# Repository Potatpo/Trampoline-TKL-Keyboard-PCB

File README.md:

# The Trampoline TKL Keyboard PCB
The trampoline tkl pcb features split spacebar, a rotary encoder, and a usb daughterboard.

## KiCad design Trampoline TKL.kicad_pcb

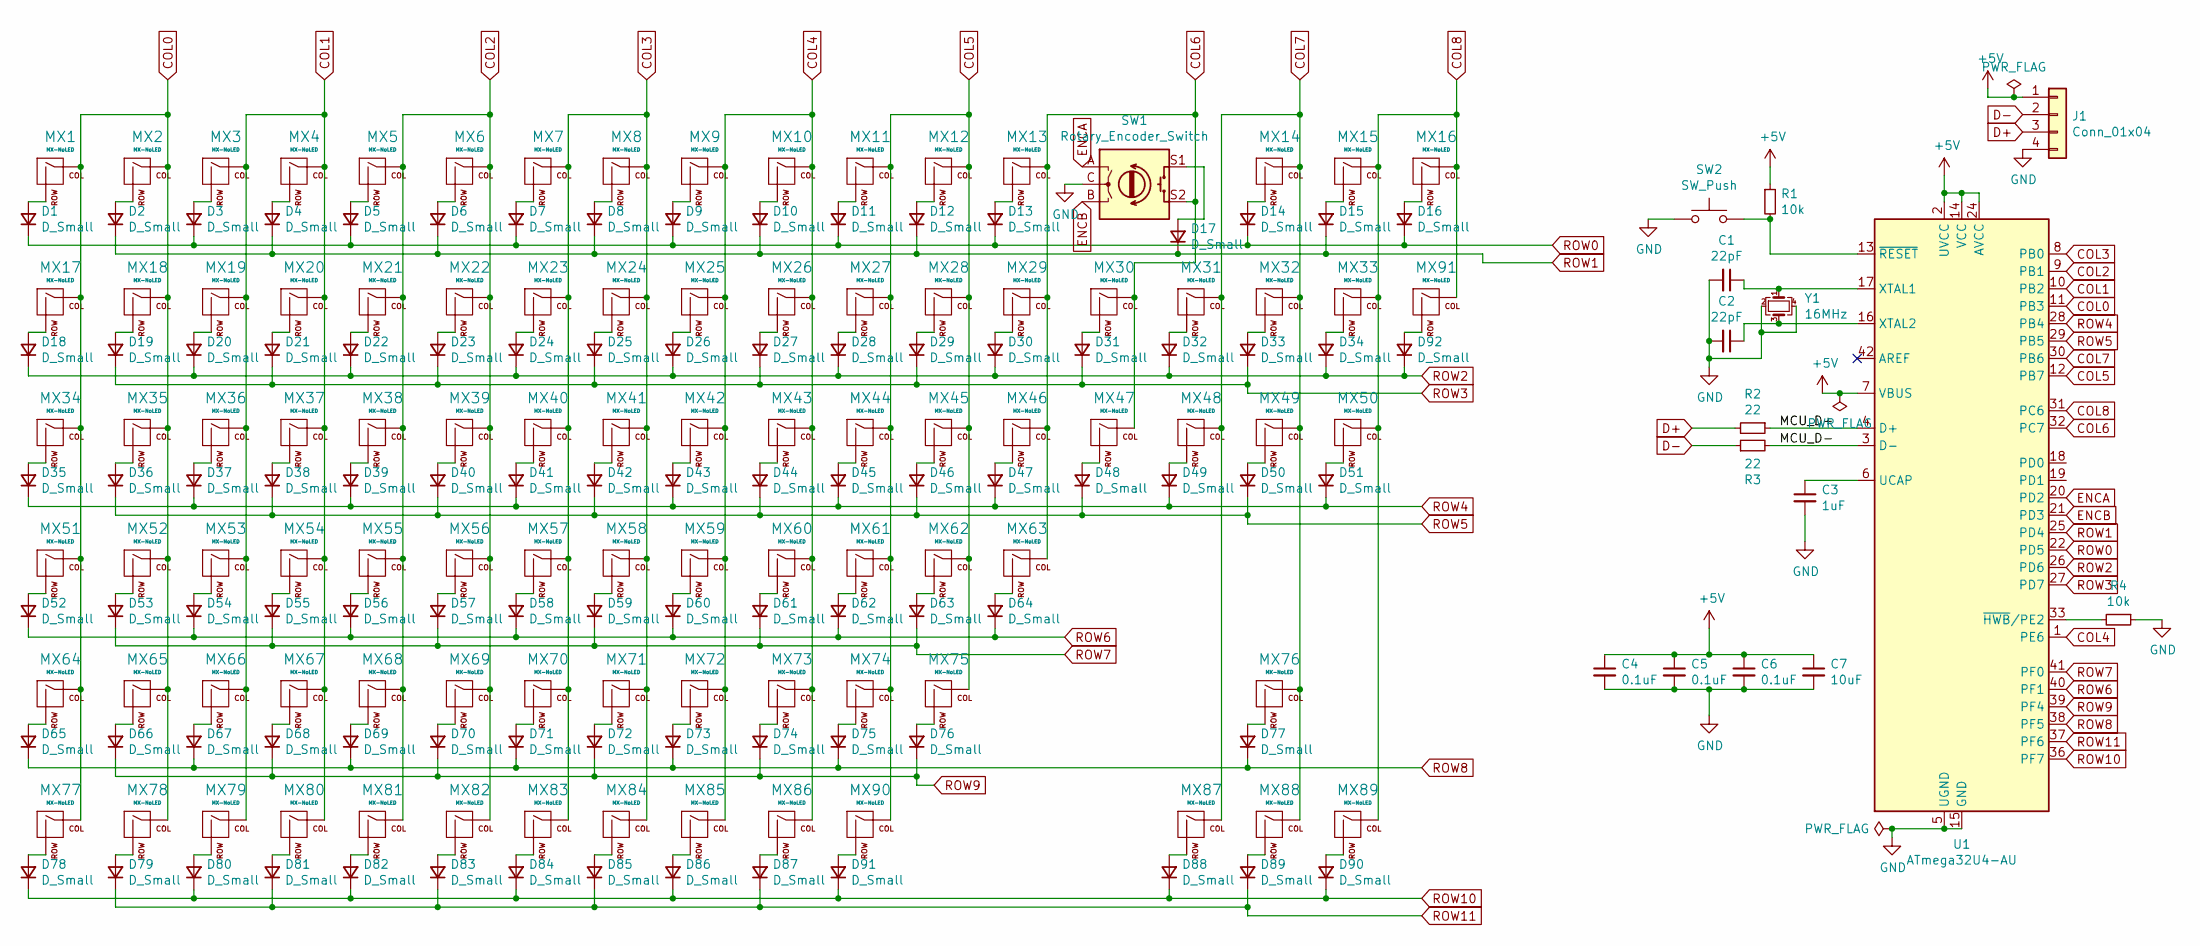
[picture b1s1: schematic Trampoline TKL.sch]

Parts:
C1, C2: 22pF; C_0805_2012Metric
C3: 1uF; C_0805_2012Metric
C4, C5, C6: 0.1uF; C_0805_2012Metric
C7: 10uF; C_0805_2012Metric
D1, D2, D3, D4, D5, D6, D7, D8, D9, D10, D11, D12, D13, D14, D15, D16, D17, D18, D19, D20, D21, D22, D23, D24, D25, D26, D27, D28, D29, D30, D31, D32, D33, D34, D35, D36, D37, D38, D39, D40, D41, D42, D43, D44, D45, D46, D47, D48, D49, D50, D51, D52, D53, D54, D55, D56, D57, D58, D59, D60, D61, D62, D63, D64, D65, D66, D67, D68, D69, D70, D71, D72, D73, D74, D75, D76, D77, D78, D79, D80, D81, D82, D83, D84, D85, D86, D87, D88, D89, D90, D91, D92: D_Small; D_SOD-123
J1: Conn_01x04; JST_SH_SM04B-SRSS-TB_1x04-1MP_P1.00mm_Horizontal
MX1, MX2, MX3, MX4, MX5, MX6, MX7, MX8, MX9, MX10, MX11, MX12, MX13, MX14, MX15, MX16, MX17, MX18, MX19, MX20, MX21, MX22, MX23, MX24, MX25, MX26, MX27, MX28, MX29, MX31, MX32, MX33, MX35, MX36, MX37, MX38, MX39, MX40, MX41, MX42, MX43, MX44, MX45, MX46, MX48, MX49, MX50, MX52, MX53, MX54, MX55, MX56, MX57, MX58, MX59, MX60, MX61, MX62, MX65, MX66, MX67, MX68, MX69, MX70, MX71, MX72, MX73, MX74, MX76, MX87, MX88, MX89, MX91: MX-NoLED; MXOnly-1U-NoLED
MX30: MX-NoLED; MXOnly-2U-NoLED
MX34, MX47: MX-NoLED; MXOnly-1.5U-NoLED
MX51: MX-NoLED; MXOnly-1.75U-NoLED
MX63, MX64, MX80: MX-NoLED; MXOnly-2.25U-NoLED
MX75, MX83: MX-NoLED; MXOnly-2.75U-NoLED
MX77, MX78, MX79, MX81, MX84, MX85, MX86, MX90: MX-NoLED; MXOnly-1.25U-NoLED
MX82: MX-NoLED; MXOnly-6.25U-NoLED
R1, R4: 10k; R_0805_2012Metric
R2, R3: 22; R_0805_2012Metric
SW1: Rotary_Encoder_Switch; RotaryEncoder_Alps_EC11E-Switch_Vertical_H20mm
SW2: SW_Push; SW_SPST_TL3342
U1: ATmega32U4-AU; TQFP-44_10x10mm_P0.8mm
Y1: 16MHz; Crystal_SMD_3225-4Pin_3.2x2.5mm

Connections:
+5V: C4.1, C5.1, C6.1, C7.1, J1.1, R1.1, U1.2 (UVCC), U1.7 (VBUS), U1.14 (VCC), U1.24 (AVCC), U1.34 (VCC), U1.44 (AVCC)
/MCU_D+: R2.1, U1.4 (D+)
/MCU_D-: R3.2, U1.3 (D-)
COL0: MX1.1 (COL), MX2.1 (COL), MX17.1 (COL), MX18.1 (COL), MX34.1 (COL), MX35.1 (COL), MX51.1 (COL), MX52.1 (COL), MX64.1 (COL), MX65.1 (COL), MX77.1 (COL), MX78.1 (COL), U1.11 (PB3)
COL1: MX3.1 (COL), MX4.1 (COL), MX19.1 (COL), MX20.1 (COL), MX36.1 (COL), MX37.1 (COL), MX53.1 (COL), MX54.1 (COL), MX66.1 (COL), MX67.1 (COL), MX79.1 (COL), MX80.1 (COL), U1.10 (PB2)
COL2: MX5.1 (COL), MX6.1 (COL), MX21.1 (COL), MX22.1 (COL), MX38.1 (COL), MX39.1 (COL), MX55.1 (COL), MX56.1 (COL), MX68.1 (COL), MX69.1 (COL), MX81.1 (COL), MX82.1 (COL), U1.9 (PB1)
COL3: MX7.1 (COL), MX8.1 (COL), MX23.1 (COL), MX24.1 (COL), MX40.1 (COL), MX41.1 (COL), MX57.1 (COL), MX58.1 (COL), MX70.1 (COL), MX71.1 (COL), MX83.1 (COL), MX84.1 (COL), U1.8 (PB0)
COL4: MX9.1 (COL), MX10.1 (COL), MX25.1 (COL), MX26.1 (COL), MX42.1 (COL), MX43.1 (COL), MX59.1 (COL), MX60.1 (COL), MX72.1 (COL), MX73.1 (COL), MX85.1 (COL), MX86.1 (COL), U1.1 (PE6)
COL5: MX11.1 (COL), MX12.1 (COL), MX27.1 (COL), MX28.1 (COL), MX44.1 (COL), MX45.1 (COL), MX61.1 (COL), MX62.1 (COL), MX74.1 (COL), MX75.1 (COL), MX90.1 (COL), U1.12 (PB7)
COL6: MX13.1 (COL), MX29.1 (COL), MX30.1 (COL), MX46.1 (COL), MX47.1 (COL), MX63.1 (COL), SW1.S2, U1.32 (PC7)
COL7: MX14.1 (COL), MX31.1 (COL), MX32.1 (COL), MX48.1 (COL), MX49.1 (COL), MX76.1 (COL), MX87.1 (COL), MX88.1 (COL), U1.30 (PB6)
COL8: MX15.1 (COL), MX16.1 (COL), MX33.1 (COL), MX50.1 (COL), MX89.1 (COL), MX91.1 (COL), U1.31 (PC6)
D+: J1.3, R2.2
D-: J1.2, R3.1
ENCA: SW1.A, U1.20 (PD2)
ENCB: SW1.B, U1.21 (PD3)
GND: C1.2, C2.2, C3.2, C4.2, C5.2, C6.2, C7.2, J1.4, R4.1, SW1.C, SW2.1, U1.5 (UGND), U1.15 (GND), U1.23 (GND), U1.35 (GND), U1.43 (GND), Y1.2, Y1.4
unnamed: C1.1, U1.17 (XTAL1), Y1.1
unnamed: C2.1, U1.16 (XTAL2), Y1.3
unnamed: C3.1, U1.6 (UCAP)
unnamed: D1.2 (A), MX1.2 (ROW)
unnamed: D2.2 (A), MX2.2 (ROW)
unnamed: D3.2 (A), MX3.2 (ROW)
unnamed: D4.2 (A), MX4.2 (ROW)
unnamed: D5.2 (A), MX5.2 (ROW)
unnamed: D6.2 (A), MX6.2 (ROW)
unnamed: D7.2 (A), MX7.2 (ROW)
unnamed: D8.2 (A), MX8.2 (ROW)
unnamed: D9.2 (A), MX9.2 (ROW)
unnamed: D10.2 (A), MX10.2 (ROW)
unnamed: D11.2 (A), MX11.2 (ROW)
unnamed: D12.2 (A), MX12.2 (ROW)
unnamed: D13.2 (A), MX13.2 (ROW)
unnamed: D14.2 (A), MX14.2 (ROW)
unnamed: D15.2 (A), MX15.2 (ROW)
unnamed: D16.2 (A), MX16.2 (ROW)
unnamed: D17.2 (A), SW1.S1
unnamed: D18.2 (A), MX17.2 (ROW)
unnamed: D19.2 (A), MX18.2 (ROW)
unnamed: D20.2 (A), MX19.2 (ROW)
unnamed: D21.2 (A), MX20.2 (ROW)
unnamed: D22.2 (A), MX21.2 (ROW)
unnamed: D23.2 (A), MX22.2 (ROW)
unnamed: D24.2 (A), MX23.2 (ROW)
unnamed: D25.2 (A), MX24.2 (ROW)
unnamed: D26.2 (A), MX25.2 (ROW)
unnamed: D27.2 (A), MX26.2 (ROW)
unnamed: D28.2 (A), MX27.2 (ROW)
unnamed: D29.2 (A), MX28.2 (ROW)
unnamed: D30.2 (A), MX29.2 (ROW)
unnamed: D31.2 (A), MX30.2 (ROW)
unnamed: D32.2 (A), MX31.2 (ROW)
unnamed: D33.2 (A), MX32.2 (ROW)
unnamed: D34.2 (A), MX33.2 (ROW)
unnamed: D35.2 (A), MX34.2 (ROW)
unnamed: D36.2 (A), MX35.2 (ROW)
unnamed: D37.2 (A), MX36.2 (ROW)
unnamed: D38.2 (A), MX37.2 (ROW)
unnamed: D39.2 (A), MX38.2 (ROW)
unnamed: D40.2 (A), MX39.2 (ROW)
unnamed: D41.2 (A), MX40.2 (ROW)
unnamed: D42.2 (A), MX41.2 (ROW)
unnamed: D43.2 (A), MX42.2 (ROW)
unnamed: D44.2 (A), MX43.2 (ROW)
unnamed: D45.2 (A), MX44.2 (ROW)
unnamed: D46.2 (A), MX45.2 (ROW)
unnamed: D47.2 (A), MX46.2 (ROW)
unnamed: D48.2 (A), MX47.2 (ROW)
unnamed: D49.2 (A), MX48.2 (ROW)
unnamed: D50.2 (A), MX49.2 (ROW)
unnamed: D51.2 (A), MX50.2 (ROW)
unnamed: D52.2 (A), MX51.2 (ROW)
unnamed: D53.2 (A), MX52.2 (ROW)
unnamed: D54.2 (A), MX53.2 (ROW)
unnamed: D55.2 (A), MX54.2 (ROW)
unnamed: D56.2 (A), MX55.2 (ROW)
unnamed: D57.2 (A), MX56.2 (ROW)
unnamed: D58.2 (A), MX57.2 (ROW)
unnamed: D59.2 (A), MX58.2 (ROW)
unnamed: D60.2 (A), MX59.2 (ROW)
unnamed: D61.2 (A), MX60.2 (ROW)
unnamed: D62.2 (A), MX61.2 (ROW)
unnamed: D63.2 (A), MX62.2 (ROW)
unnamed: D64.2 (A), MX63.2 (ROW)
unnamed: D65.2 (A), MX64.2 (ROW)
unnamed: D66.2 (A), MX65.2 (ROW)
unnamed: D67.2 (A), MX66.2 (ROW)
unnamed: D68.2 (A), MX67.2 (ROW)
unnamed: D69.2 (A), MX68.2 (ROW)
unnamed: D70.2 (A), MX69.2 (ROW)
unnamed: D71.2 (A), MX70.2 (ROW)
unnamed: D72.2 (A), MX71.2 (ROW)
unnamed: D73.2 (A), MX72.2 (ROW)
unnamed: D74.2 (A), MX73.2 (ROW)
unnamed: D75.2 (A), MX74.2 (ROW)
unnamed: D76.2 (A), MX75.2 (ROW)
unnamed: D77.2 (A), MX76.2 (ROW)
unnamed: D78.2 (A), MX77.2 (ROW)
unnamed: D79.2 (A), MX78.2 (ROW)
unnamed: D80.2 (A), MX79.2 (ROW)
unnamed: D81.2 (A), MX80.2 (ROW)
unnamed: D82.2 (A), MX81.2 (ROW)
unnamed: D83.2 (A), MX82.2 (ROW)
unnamed: D84.2 (A), MX83.2 (ROW)
unnamed: D85.2 (A), MX84.2 (ROW)
unnamed: D86.2 (A), MX85.2 (ROW)
unnamed: D87.2 (A), MX86.2 (ROW)
unnamed: D88.2 (A), MX87.2 (ROW)
unnamed: D89.2 (A), MX88.2 (ROW)
unnamed: D90.2 (A), MX89.2 (ROW)
unnamed: D91.2 (A), MX90.2 (ROW)
unnamed 111: D92.2 (A), MX91.2 (ROW); also elsewhere on the board
unnamed: R1.2, SW2.2, U1.13 (~RESET)
unnamed: R4.2, U1.33 (~HWB~/PE2)
ROW0: D1.1 (K), D3.1 (K), D5.1 (K), D7.1 (K), D9.1 (K), D11.1 (K), D13.1 (K), D14.1 (K), D16.1 (K), U1.22 (PD5)
ROW1: D2.1 (K), D4.1 (K), D6.1 (K), D8.1 (K), D10.1 (K), D12.1 (K), D15.1 (K), D17.1 (K), U1.25 (PD4)
ROW2: D18.1 (K), D20.1 (K), D22.1 (K), D24.1 (K), D26.1 (K), D28.1 (K), D30.1 (K), D32.1 (K), D34.1 (K), D92.1 (K), U1.26 (PD6); also elsewhere on the board
ROW3: D19.1 (K), D21.1 (K), D23.1 (K), D25.1 (K), D27.1 (K), D29.1 (K), D31.1 (K), D33.1 (K), U1.27 (PD7)
ROW4: D35.1 (K), D37.1 (K), D39.1 (K), D41.1 (K), D43.1 (K), D45.1 (K), D47.1 (K), D49.1 (K), D51.1 (K), U1.28 (PB4)
ROW5: D36.1 (K), D38.1 (K), D40.1 (K), D42.1 (K), D44.1 (K), D46.1 (K), D48.1 (K), D50.1 (K), U1.29 (PB5)
ROW6: D52.1 (K), D54.1 (K), D56.1 (K), D58.1 (K), D60.1 (K), D62.1 (K), D64.1 (K), U1.40 (PF1)
ROW7: D53.1 (K), D55.1 (K), D57.1 (K), D59.1 (K), D61.1 (K), D63.1 (K), U1.41 (PF0)
ROW8: D65.1 (K), D67.1 (K), D69.1 (K), D71.1 (K), D73.1 (K), D75.1 (K), D77.1 (K), U1.38 (PF5)
ROW9: D66.1 (K), D68.1 (K), D70.1 (K), D72.1 (K), D74.1 (K), D76.1 (K), U1.39 (PF4)
ROW10: D78.1 (K), D80.1 (K), D82.1 (K), D84.1 (K), D86.1 (K), D88.1 (K), D90.1 (K), D91.1 (K), U1.36 (PF7)
ROW11: D79.1 (K), D81.1 (K), D83.1 (K), D85.1 (K), D87.1 (K), D89.1 (K), U1.37 (PF6)

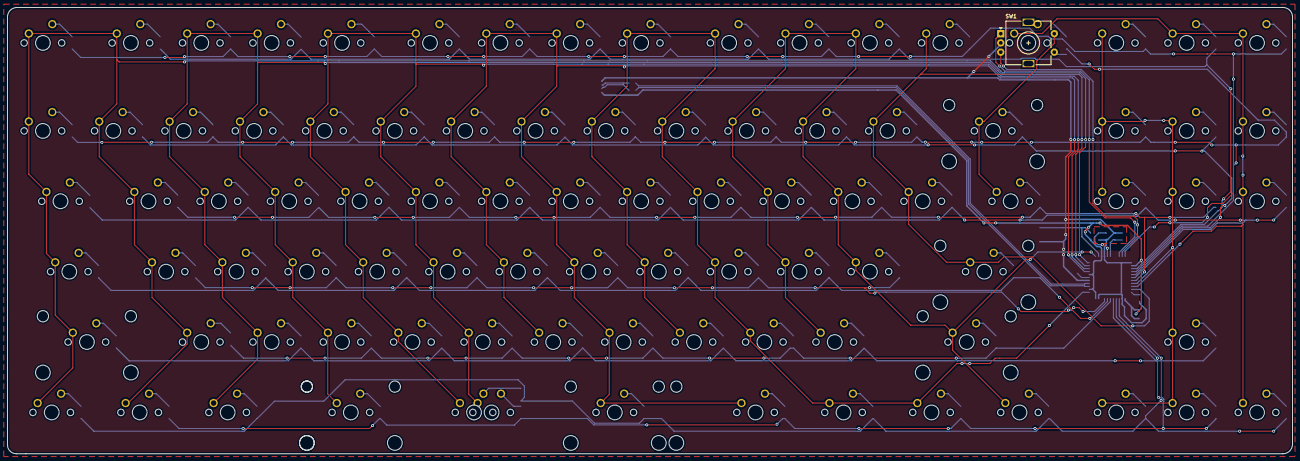
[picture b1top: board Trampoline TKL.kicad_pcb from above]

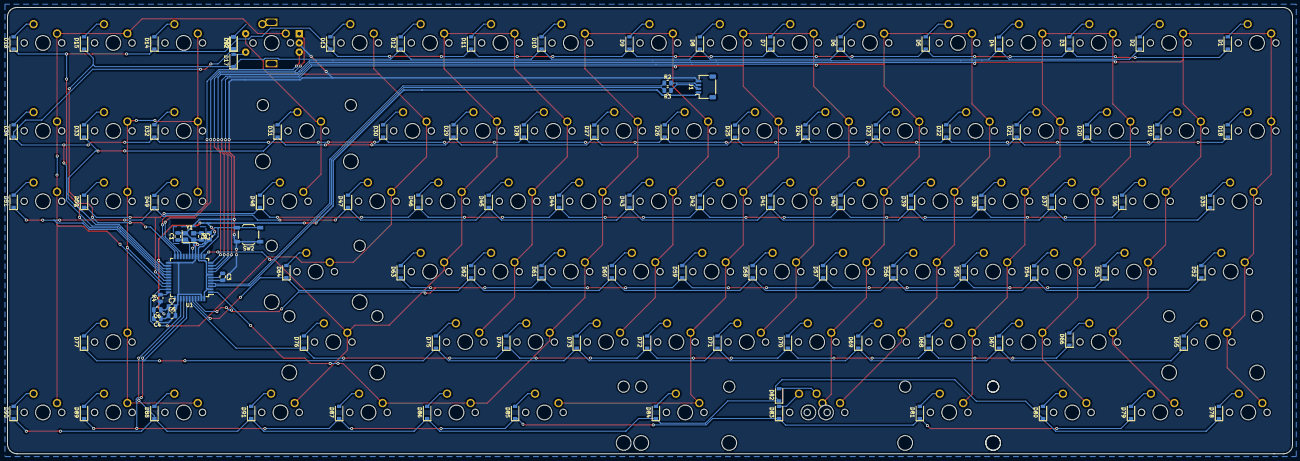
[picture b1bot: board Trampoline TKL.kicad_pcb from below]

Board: 2 copper layers, 347.8 x 120.8 mm, 200 parts (108 on the bottom side), 126 nets.

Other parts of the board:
D92#2: D_Small; D_SOD-123

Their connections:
unnamed 111: D92#2.2; also elsewhere on the board
ROW2: D92#2.1; also elsewhere on the board

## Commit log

2021-10-23 starting it off
2021-10-30 asddff
2021-10-30 adsasdasd
